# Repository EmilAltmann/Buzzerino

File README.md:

# Buzzerino

This is the repository of the soldering kit by the Digital Technology Group at the University of Kassel.

The contents of this document:
* [Soldering Instructions](#soldering-instructions)
* [Flashing](#flashing)
* [Example Programs](#example-programs)
* [How to Code / Work with AI](#how-to-code-and-work-with-ai)
* [Parts and Wiki](#parts-and-wiki)

## Soldering Instructions

We created a short video about the assembly process:

### Bill of Materials
Please check if you have all the necessary components listed below:
* 1x Buzzerino circuit board (Buzzerino PCB)
* 1x Raspberry Pi Pico
* 1x 1602A LCD display
* 1x AHT10 digital temperature and humidity sensor
* 1x USB-C breakout board
* 1x 10 mm RGB LED
* 1x buzzer
* 1x analogue joystick
* 5x 6 mm push buttons
* 1x 100 kΩ NTC temperature-dependent resistor
* 5x 330 Ω resistors
* 1x 1 kΩ resistor
* 1x 10 kΩ resistor
* 1x 120 kΩ resistor
* 2x 1x20 pin headers and sockets (keep them plugged together)
* 1x 1x16 pin header
* 2x 1x4 pin headers
* 1x 1x3 pin header
* 1x 2x16 pin header
* 1x 2x7 pin header
* 1x 2x3 pin header
* 26x jumper

### Assembly of the Raspberry Pi Pico

We will start by soldering the two 1x20 pin headers and sockets to the Raspberry Pi Pico board. The pin strips are each two parts plugged together; keep them together, as this will keep the contacts aligned! The side with the slimmer plastic piece will be soldered to the Raspberry Pi Pico (in the picture above, the inner one).

Start by putting the pin headers into the Raspberry Pi Pico and the Buzzerino PCB. The Raspberry Pi Pico should sit flat and parallel on both pin strips.

Now we can solder our first connections. Heat one of the corner pins with your soldering iron. Check with solder whether the joint is up to temperature by gently feeding it into the heated pin. If the solder melts, you can remove the soldering iron and let the connection cool down.

Continue by soldering the three other corners.

Now you can remove the Raspberry Pi Pico from the Buzzerino PCB (with the pin headers still together).

With the Raspberry Pi Pico now free, but the pin strips still attached to it, you can fully solder both sides.

### Assembly of the USB-C breakout board

Now we will solder the 1x4 pin header to the USB-C breakout board. Because both pieces are very small, it's a good tactic to plug them together and place them on your table.

Start by soldering only one pin, as the angle between the board and the pin header will likely be slightly crooked.

To correct the angle of the pin header, hold both pieces together and carefully reheat the solder joint. Now you can correct any misalignment. Once the pins are perpendicular to the board, solder all four pins.

### Assembly of the AHT10 digital temperature sensor

The assembly of the AHT10 digital temperature sensor is identical to that of the USB-C breakout board. Start by soldering only one pin and correct the alignment so it is nice and perpendicular.

### Assembly of the 1602A LCD display

The assembly of the 1602A LCD display is very similar to the previous two steps. First solder one pin, check for squareness and correct, then solder all pins.

### Installation of resistors
#### 100 kΩ NTC temperature-dependent resistor

The 100 kΩ NTC temperature-dependent resistor has a glass body with no markings.

The resistors come with straight leads and need to be formed. For that purpose hold them with one hand between two fingers and pull them to a U-shape with your other hand as seen in the following pictures:

The newly formed resistor can now be inserted into the Buzzerino PCB at the position marked TH_NTC.
**Important:** The printed side of the Buzzerino PCB is the front of the PCB. The lower left corner should have our DIGETEC logo!

As a tip for soldering beginners, you can slightly bend the leads outwards after fully seating the resistor. This will help keep it in place.

Like the previous solder joints, it's good practice to start by soldering one lead first, then correct the positioning, and finally solder both.

After the resistor is fully seated, you can clip the leads flush with side cutters.

#### 1 kΩ resistor

The 1 kΩ resistor has stripes as markings (Brown | Black | Red | | Gold).

The installation of the different resistors is essentially identical. For the 1 kΩ resistor, start by forming it roughly U-shaped.

Then place it in its position, solder one leg, correct the placement, solder completely, and clip the leads flush.

#### 10 kΩ resistor

The 10 kΩ resistor has stripes as markings (Brown | Black | Orange | | Gold).

For the 10 kΩ resistor: form, place, solder one leg, correct, solder fully, and clip flush.

#### 330 Ω resistors

The 330 Ω resistors hve stripes as markings (Orange | Orange | Black | Black | Brown).

For the 330 Ω resistors: form, place, solder one leg, correct, solder fully, and clip flush.

#### 120 kΩ resistor

The 120 kΩ resistor has stripes as markings (Brown | Red | Yellow | | Gold).

For the 120 kΩ resistor: form, place, solder one leg, correct, solder fully, and clip flush.

### Installation of the buttons

For the assembly of the Buzzerino PCB, we will go from the shortest to the highest component. This helps you successfully solder your board.

The shape of the button legs is designed to snap into the Buzzerino PCB. After placing the buttons, check if they sit flush to the Buzzerino PCB. Then solder and clip the leads.

With the D-pad buttons it's the same procedure as with the reset button.

### Soldering the pin header

**Repeated Error: The short side shall go through the board!**

We start by soldering the 2x7 pin header to the Buzzerino PCB. **The short side shall go through the board.**

As with all the previous solder joints, it's best practice to first solder one pin and then check for alignment. The wider pin header will often move a bit out of the Buzzerino PCB and may need to be reseated. Only after the pin headers are placed completely in position should you solder the remaining pins.

Repeat the previous step for the 2x3 and 2x16 pin headers. Start by soldering one pin, then check and correct the seating, and then solder completely.

The 1x3 pin header is one of the fiddliest to install. With all the previous practice, you will be able to solder it flush and perpendicular.

### Installation of the USB-C breakout board

Now we can solder the USB-C breakout board. After placing it into position (right side of the Buzzerino PCB, facing outwards, the usb port shuld be fully visible), solder one pin. Then check for alignment; it should be parallel to the Buzzerino PCB. Then solder it completely.

**WARNING:** The pins of the USB-C breakout board, the AHT10 temperature sensor, and the 1602A LCD display are too hard for electronics side cutters! Use larger wire cutters as provided.

### Installation of the AHT10 digital temperature sensor

The installation of the AHT10 digital temperature sensor is analogous to the USB-C breakout board (Position left side of the Buzzerino PCB, facing upwards, the components of the sub-PCB sould be visible). But remember: use the larger wire cutters for cutting the pins to length.

### Installation of the Buzzer

Finally, we can install the namesake of the board. This is our first polarized component. The footprint on the Buzzerino PCB shows a small +. Furthermore, the sticker on the buzzer has a plus on its top. These should be aligned. (If you look from the front of the Buzzerino PCB, the plus will be facing inwards.) Moreover, if you are unsure, you can check the buzzer's leads: one of them is longer than the other. This is the positive lead and shall align with the plus symbol on the Buzzerino PCB.

### Installation of the 1602A LCD display

The installation of the 1602A LCD display is analogous to the USB-C breakout board. First place, then solder one pin, then check for alignment and then solder fully. But remember: use the larger wire cutters for cutting the pins to length.

### Installation of the RGB LED

Now we can install the RGB LED.

The LED is, like the buzzer, polarized. But here the longest leg is the negative connection. The footprint on the Buzzerino PCB indicates the negative connection with a square pad. Place the LED into its position. The spacing of the pads is a bit wider than the lead spacing, so the leads will spread out automatically.

After soldering and cutting the RGB LED's leads flush, you will probably have a very ugly joint. Luckily, you can easily correct this by slowly running your soldering iron between two pins and letting them reflow. The surface tension of the solder should pull the joint nicely together, resulting in a clean joint. But check for any bridges after that! If there are any, clean your soldering tip and repeat the reflow.

### Installation of the Raspberry Pi Pico

Now we can install the Raspberry Pi Pico. As with all previous complex connections, start by soldering only two opposite pins. Then check for alignment; after that, solder completely.

### Installation of the analogue joystick

As the last component, we will install the analogue joystick.

The installation of the joystick can be harder than necessary because of the many different pins. Start by putting the push-button pins into the Buzzerino PCB and then wiggle each pin from left to right slowly into position. After the joystick is fully seated, you can solder it in place.

### Installation of the jumpers

Before testing the board, we need to install all 26 jumpers as seen in the picture above.

**Congratulations, you have finished your soldering project.**

If you already flashed your Raspberry Pi Pico, it's time to power it up; if not, flash the self_test.uf2 onto the board.

## Flashing

If the board is not connected to a power source:
Press and hold the BOOTSEL button on the Raspberry Pi Pico and connect it via micro-USB to a PC. The Pico should mount as a mass-storage device called RPI-RP2. Now you can drag and drop a previously compiled or downloaded .uf2 file onto it. It will automatically unmount and reboot. Ignore the message from your PC that the device was disconnected without ejecting.
You don't need to unplug and replug the Raspberry Pi Pico every time you want to flash it. You can also, with an established connection to your PC, press and hold the BOOTSEL button on the Raspberry Pi Pico and then briefly press (while still holding the BOOTSEL button) the SW_RESET button on the Buzzerino PCB.

## Example Programs

The code of the example programs and their .uf2 files are available in the folder example_programs. Unless otherwise noted, all programs are designed and compiled for the Raspberry Pi Pico (neither the W version nor version 2) but can be recompiled for these targets. The preferred way to compile is VS Code with the Raspberry Pi Pico extension.

## How to Code and Work with AI

You can code the Raspberry Pi Pico using the Arduino IDE or Microsoft Visual Studio Code (VS Code) with the Raspberry Pi Pico extension. If you use the Arduino IDE, you need to install the necessary board support as described in the [blog post from Random Nerd Tutorials](https://randomnerdtutorials.com/programming-raspberry-pi-pico-w-arduino-ide/).
We provide a comprehensive AI guidance document for users who want to use AI tools for programming, installation, or debugging. You can include the [AI_GUIDELINES.md](https://github.com/EmilAltmann/Buzzerino/blob/main/AI_GUIDELINES.md) file in your conversation with a chat-based AI assistant and ask it to follow the instructions closely.

If possible, we recommend attaching the document directly to the conversation rather than pasting only parts of it. This helps ensure that the AI still has access to the full context and instructions, even in longer conversations.

## Parts and Wiki

### Raspberry Pi Pico
The core of the whole board is a [Raspberry Pi Pico microcontroller](https://www.raspberrypi.com/products/raspberry-pi-pico/). It can be programmed as described in the [How to Code](#how-to-code) section. The SW_RESET button to the left of the microcontroller can be used to reset the microcontroller.

### 1602A LCD display
The display is a 16-character by 2-row LCD. It is connected via a parallel bus to the Raspberry Pi Pico. The [datasheet](https://www.openhacks.com/uploadsproductos/eone-1602a1.pdf) explains its function as it is implemented in the example program. Because the display works on 5 V and the Raspberry Pi Pico on 3.3 V, you can only write to the display and the read/write pin is always set to write (tied low).
The pinout is as follows:
| GPIO | LCD |
|------|-----|
| 6    | D7  |
| 7    | D6  |
| 8    | D5  |
| 9    | D4  |
| 10   | D3  |
| 11   | D2  |
| 12   | D1  |
| 13   | D0  |
| 14   | E   |
| 15   | RS  |

### AHT10 temperature and humidity sensor
The AHT10 digital temperature and humidity sensor is connected via I2C to the Raspberry Pi Pico. It has the address 0x38 and can be accessed as described in the [datasheet](https://server4.eca.ir/eshop/AHT10/Aosong_AHT10_en_draft_0c.pdf). It is connected to the I2C0 interface on the Raspberry Pi Pico.
The pinout is as follows:
| GPIO | AHT10 |
|------|-------|
| 0    | SDA   |
| 1    | SCL   |

### Buzzer
The buzzer is an active 4.5 kHz buzzer. It is connected to GPIO pin 19 on the Raspberry Pi Pico. Active means it contains a driver and will produce this tone when powered. You can chop the sound using PWM to reproduce different sound effects.

### D-pad buttons
The D-pad buttons can be used as a generic input. They are connected directly to a digital pin of the Raspberry Pi Pico without any filter or pull-up or pull-down resistors. So the internal pull-up resistors need to be activated and debounce logic needs to be implemented in software.
The pinout is as follows:
| GPIO | Button |
|------|--------|
| 2    | up     |
| 3    | down   |
| 4    | left   |
| 5    | right  |

### Analogue joystick
The analogue joystick can be used as a fine-grained input. It is connected to the 12-bit analogue-to-digital converter (ADC) of the Raspberry Pi Pico. It has two axes and a push-button. The X-axis measures the up/down angle between 0 (fully down) and 4095 (fully up), the Y-axis measures correspondingly the left/right angle between 0 (fully left) and 4095 (fully right). Due to manufacturing tolerances, the exact midpoint and extrema should be determined experimentally. The push-button is, like the D-pad buttons, directly connected to a digital pin of the Raspberry Pi Pico.
The pinout is as follows:
| GPIO      | Joystick |
|-----------|----------|
| 18        | button   |
| 31 (ADC0) | X-axis   |
| 32 (ADC1) | Y-axis   |

### RGB LED
The RGB LED is connected to three pins of the Raspberry Pi Pico. It can be dimmed via the PWM function as seen in the example program.
The pinout is as follows:
| GPIO | LED |
|------|-----|
| 20   | R   |
| 21   | G   |
| 22   | B   |

### 100 kΩ NTC analogue temperature sensor
The 100 kΩ NTC analogue temperature sensor is a second way to measure the temperature of the surroundings. It is connected to the 12-bit analogue-to-digital converter (ADC) of the Raspberry Pi Pico like the potentiometers of the joystick. It is configured in a voltage divider with a 120 kΩ pull-down resistor and a 3.3 V positive connection. The midpoint is connected to pin 28 (ADC2) on the Raspberry Pi Pico. Its B-value is 3950 K and its resistance is 100 kΩ at 25 °C.

### USB-C power connector
The USB-C power connector can be used as an alternative way to power the board. For example, it's necessary if you want to use the Raspberry Pi Pico as a USB host for a keyboard.
**KNOWN ISSUES:** The USB-C connector doesn't completely comply with the standard, so some smart USB chargers don't recognize the board as a valid device. Just use a cable without data connections or try another charger.

### Breakout / Jumper pins
The board has three blocks of jumper pins. They connect the GPIO pins from the Raspberry Pi Pico to the peripherals. The inner row represents the GPIO, the outer the periphery. If you want to disable or reconfigure functions of the board, you can do this by means of jumper cables. Moreover, the board has a 3-pin connector which can be used as a ground and power connection to the 5 V and 3.3 V rails.

### UART Interface
If you want to communicate via a serial interface with the board, you can use UART. There are two options available. The first one is the micro-USB port on the Raspberry Pi Pico, the second is the two pins marked as UART0 TX and UART0 RX. These are connected to the GPIO pins and can be connected to other UART devices or via a USB–serial converter.

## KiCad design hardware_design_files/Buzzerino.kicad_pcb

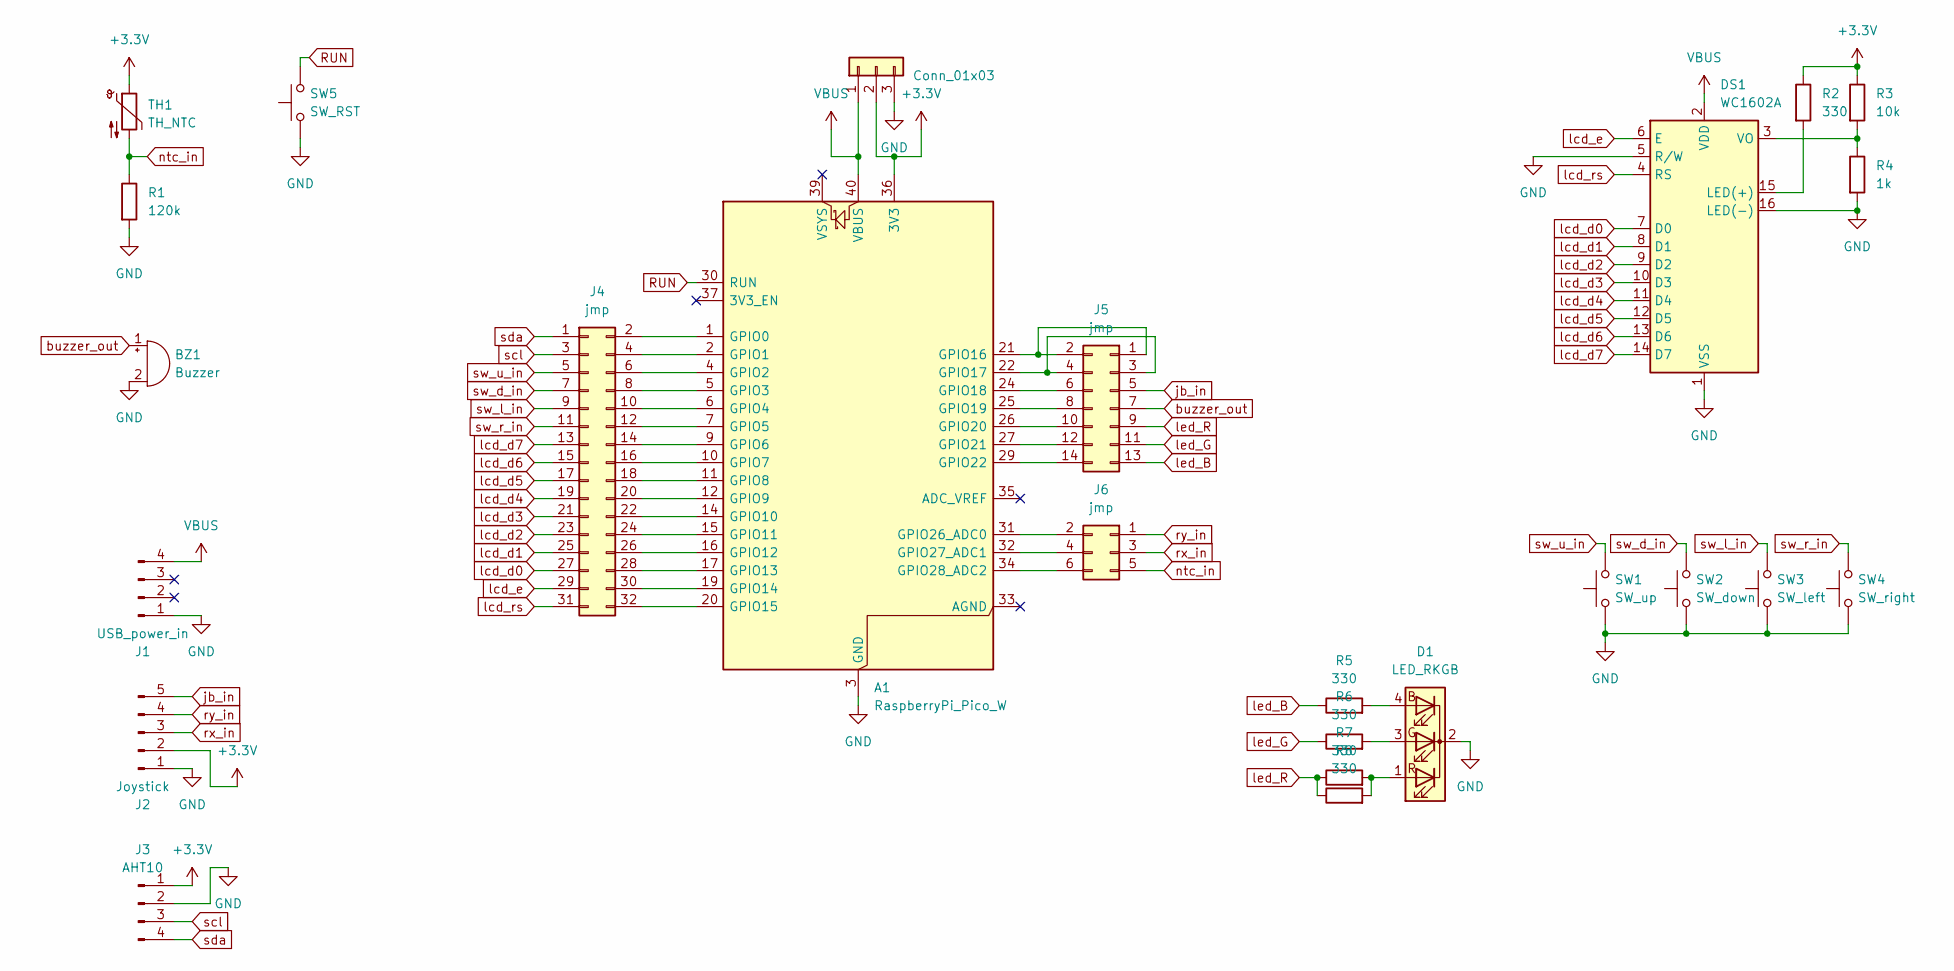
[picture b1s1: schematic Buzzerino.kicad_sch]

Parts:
A1: RaspberryPi_Pico_W; RaspberryPi_Pico_Common_THT
BZ1: Buzzer; Buzzer_12x9.5RM7.6
D1: LED_RKGB; led_D10mm_4pin
DS1: WC1602A
J1: USB_power_in; PinHeader_1x04_P2.54mm_Vertical
J2: Joystick; PS4_joystick
J3: AHT10; PinHeader_1x04_P2.54mm_Vertical
J4: jmp; PinHeader_2x16_P2.54mm_Vertical
J5: jmp; PinHeader_2x07_P2.54mm_Vertical
J6: jmp; PinHeader_2x03_P2.54mm_Vertical
J8: Conn_01x03; PinHeader_1x03_P2.54mm_Vertical
R1: 120k; R_Axial_DIN0207_L6.3mm_D2.5mm_P10.16mm_Horizontal
R2, R5, R6, R7, R8: 330; R_Axial_DIN0207_L6.3mm_D2.5mm_P10.16mm_Horizontal
R3: 10k; R_Axial_DIN0207_L6.3mm_D2.5mm_P10.16mm_Horizontal
R4: 1k; R_Axial_DIN0207_L6.3mm_D2.5mm_P10.16mm_Horizontal
SW1: SW_up; SW_PUSH_6mm
SW2: SW_down; SW_PUSH_6mm
SW3: SW_left; SW_PUSH_6mm
SW4: SW_right; SW_PUSH_6mm
SW5: SW_RST; SW_PUSH_6mm
TH1: TH_NTC; R_Axial_DIN0207_L6.3mm_D2.5mm_P10.16mm_Horizontal

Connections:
+3.3V: A1.36 (3V3), J2.2, J3.1, J8.2, R2.1, R3.1, TH1.1
GND: A1.3 (GND), A1.8 (GND), A1.13 (GND), A1.18 (GND), A1.23 (GND), A1.28 (GND), A1.38 (GND), BZ1.2 (-), D1.2 (K), DS1.1 (VSS), DS1.5 (R/W), DS1.16 (LED(-)), J1.1, J2.1, J3.2, J8.3, R1.2, R4.2, SW1.1, SW2.1, SW3.1, SW4.1, SW5.1
unnamed: A1.1 (GPIO0), J4.2
unnamed: A1.2 (GPIO1), J4.4
unnamed: A1.4 (GPIO2), J4.6
unnamed: A1.5 (GPIO3), J4.8
unnamed: A1.6 (GPIO4), J4.10
unnamed: A1.7 (GPIO5), J4.12
unnamed: A1.9 (GPIO6), J4.14
unnamed: A1.10 (GPIO7), J4.16
unnamed: A1.11 (GPIO8), J4.18
unnamed: A1.12 (GPIO9), J4.20
unnamed: A1.14 (GPIO10), J4.22
unnamed: A1.15 (GPIO11), J4.24
unnamed: A1.16 (GPIO12), J4.26
unnamed: A1.17 (GPIO13), J4.28
unnamed: A1.19 (GPIO14), J4.30
unnamed: A1.20 (GPIO15), J4.32
unnamed: A1.21 (GPIO16), J5.1, J5.2
unnamed: A1.22 (GPIO17), J5.3, J5.4
unnamed: A1.24 (GPIO18), J5.6
unnamed: A1.25 (GPIO19), J5.8
unnamed: A1.26 (GPIO20), J5.10
unnamed: A1.27 (GPIO21), J5.12
unnamed: A1.29 (GPIO22), J5.14
unnamed: A1.31 (GPIO26_ADC0), J6.2
unnamed: A1.32 (GPIO27_ADC1), J6.4
unnamed: A1.34 (GPIO28_ADC2), J6.6
unnamed: D1.4 (BA), R5.2
unnamed: D1.3 (GA), R6.2
unnamed: D1.1 (RA), R7.2, R8.2
unnamed: DS1.15 (LED(+)), R2.2
unnamed: DS1.3 (VO), R3.2, R4.1
RUN: A1.30 (RUN), SW5.2
VBUS: A1.40 (VBUS), DS1.2 (VDD), J1.4, J8.1
buzzer_out: BZ1.1 (+), J5.7
jb_in: J2.5, J5.5
lcd_d0: DS1.7 (D0), J4.27
lcd_d1: DS1.8 (D1), J4.25
lcd_d2: DS1.9 (D2), J4.23
lcd_d3: DS1.10 (D3), J4.21
lcd_d4: DS1.11 (D4), J4.19
lcd_d5: DS1.12 (D5), J4.17
lcd_d6: DS1.13 (D6), J4.15
lcd_d7: DS1.14 (D7), J4.13
lcd_e: DS1.6 (E), J4.29
lcd_rs: DS1.4 (RS), J4.31
led_B: J5.13, R5.1
led_G: J5.11, R6.1
led_R: J5.9, R7.1, R8.1
ntc_in: J6.5, R1.1, TH1.2
rx_in: J2.3, J6.3
ry_in: J2.4, J6.1
scl: J3.3, J4.3
sda: J3.4, J4.1
sw_d_in: J4.7, SW2.2
sw_l_in: J4.9, SW3.2
sw_r_in: J4.11, SW4.2
sw_u_in: J4.5, SW1.2

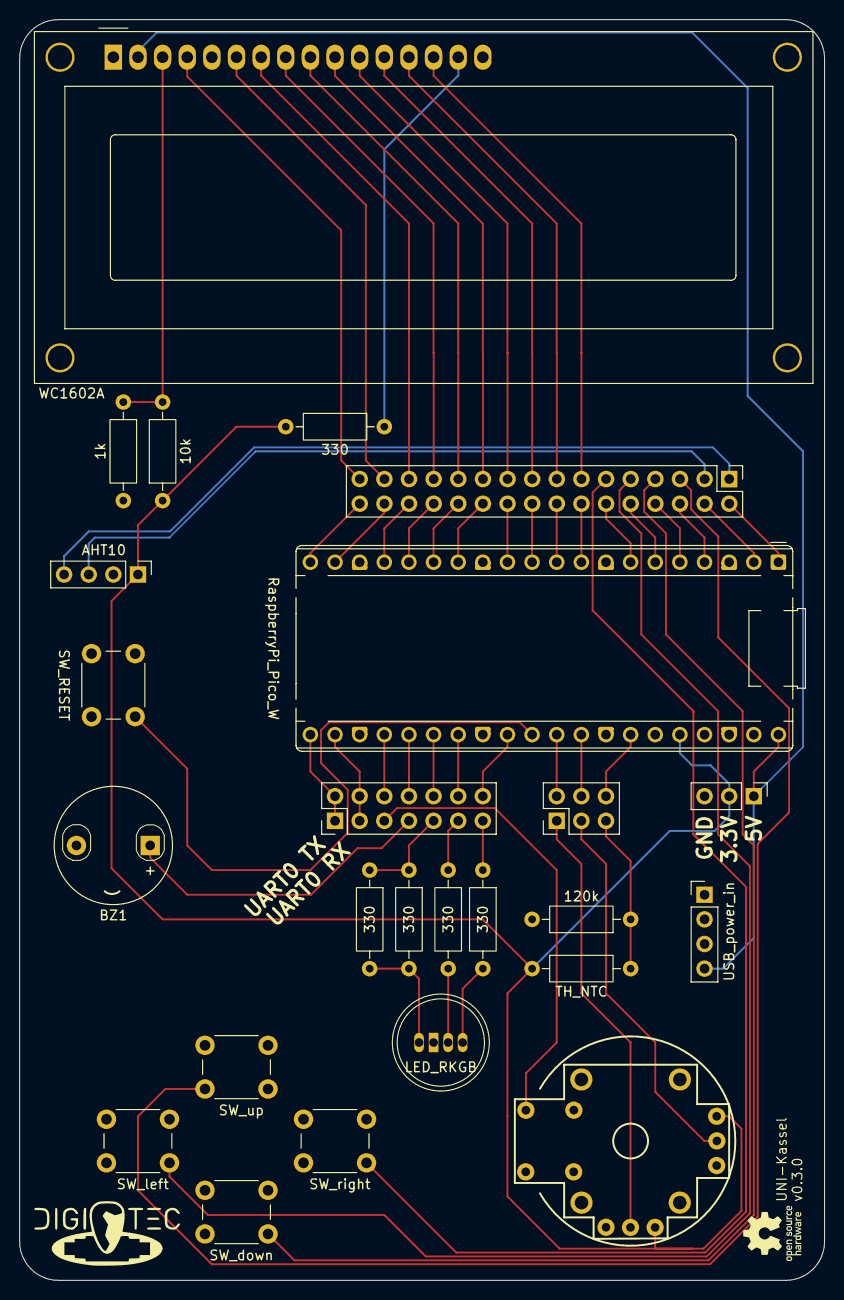
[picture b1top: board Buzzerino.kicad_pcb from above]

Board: 2 copper layers, 83.0 x 130.0 mm, 25 parts (0 on the bottom side), 59 nets.

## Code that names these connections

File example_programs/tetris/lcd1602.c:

#include "lcd1602.h"
#include "pico/stdlib.h"
#include "hardware/gpio.h"

#define LCD_D7 6
#define LCD_D6 7
#define LCD_D5 8
#define LCD_D4 9
#define LCD_D3 10
#define LCD_D2 11
#define LCD_D1 12
#define LCD_D0 13

#define LCD_E 14
#define LCD_RS 15

static uint8_t _disp_ctrl = 0x0C; // D=1, C=0, B=0

static void lcd_pulse_e(void)
{
    gpio_put(LCD_E, 1);
    sleep_us(1); // ≥ 450 ns
    gpio_put(LCD_E, 0);
}

static void lcd_write8(uint8_t val)
{
    gpio_put(LCD_D0, val & 0x01);
    gpio_put(LCD_D1, val & 0x02);
    gpio_put(LCD_D2, val & 0x04);
    gpio_put(LCD_D3, val & 0x08);
    gpio_put(LCD_D4, val & 0x10);
    gpio_put(LCD_D5, val & 0x20);
    gpio_put(LCD_D6, val & 0x40);
    gpio_put(LCD_D7, val & 0x80);
    lcd_pulse_e();
}

static void lcd_cmd(uint8_t cmd)
{
    gpio_put(LCD_RS, 0);
    lcd_write8(cmd);

    if (cmd == 0x01 || cmd == 0x02)
        sleep_ms(2);
    else
        sleep_us(50);
}

static void lcd_data(uint8_t data)
{
    gpio_put(LCD_RS, 1);
    lcd_write8(data);
    sleep_us(50);
}

void lcd_init(void)
{
    const uint lcd_pins[] = {
        LCD_D0, LCD_D1, LCD_D2, LCD_D3, LCD_D4, LCD_D5, LCD_D6, LCD_D7,
        LCD_E, LCD_RS};

    for (uint i = 0; i < sizeof(lcd_pins) / sizeof(lcd_pins[0]); ++i)
    {
        gpio_init(lcd_pins[i]);
        gpio_set_dir(lcd_pins[i], GPIO_OUT);
        gpio_put(lcd_pins[i], 0);
    }

    sleep_ms(20);

    lcd_cmd(0x38);       // 8-bit | 2 lines | 5x8
    lcd_cmd(0x08);       // display off
    lcd_cmd(0x01);       // clear
    lcd_cmd(0x06);       // entry mode
    lcd_cmd(_disp_ctrl); // display on
}

void lcd_putc(char c) { lcd_data((uint8_t)c); }

void lcd_puts(const char *s)
{
    while (*s) lcd_putc(*s++);
}

void lcd_cursor_visible(uint8_t on)
{
    if (on) _disp_ctrl |= 0x02;
    else    _disp_ctrl &= ~0x02;
    lcd_cmd(_disp_ctrl);
}

void lcd_cursor_blink(uint8_t on)
{
    if (on) _disp_ctrl |= 0x01;
    else    _disp_ctrl &= ~0x01;
    lcd_cmd(_disp_ctrl);
}

void lcd_cursor_left(void)  { lcd_cmd(0x10); }
void lcd_cursor_right(void) { lcd_cmd(0x14); }

void lcd_gotoxy(uint8_t row, uint8_t col)
{
    static const uint8_t row_addr[2] = {0x00, 0x40};
    lcd_cmd(0x80 | (row_addr[row & 1] + (col & 0x0F)));
}

void lcd_create_char(uint8_t slot, const uint8_t bitmap[8])
{
    slot &= 0x07;
    lcd_cmd(0x40 | (slot << 3));   // CGRAM address
    for (int i = 0; i < 8; i++) {
        lcd_data(bitmap[i] & 0x1F); // nur 5 Bit relevant
    }
    lcd_cmd(0x80); // zurück zu DDRAM
}

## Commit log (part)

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2025-10-24 Inital commit of bulding instruction and self_test programm as well as schematic and pcb layout files.
2025-10-24 fixed image paths
2025-10-24 fixed some wrong picture
2025-11-03 cleaned some steps in the building instructons
2025-11-03 Added desription of resistor markings
2025-11-03 fix transparent background on DigiTec logo
2026-01-20 Added multiple example games
2026-01-28 Added weather station example.
2026-01-28 fixed typo
2026-04-02 Add assembly video and image to README
    Added a video link and image for assembly instructions.
2026-04-13 add video thumbnail
2026-04-13 fixed video preview link
2026-04-13 edited video Thumbnail
2026-04-13 adding AI_Guidelines document
2026-04-13 adding explanation of AI-GUIDELINES to README
2026-04-26 added latex and pdf instructions in english, german and simple german
2026-04-27 cleaned postion of latex and pdf
2026-04-27 add buzeriono os
